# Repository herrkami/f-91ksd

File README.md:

# F-91KSD

F-91KSD is a functional and optical modification of the Casio® F-91W.

**Hardware and firmware are heavily based on the brilliant
[pluto](https://github.com/carrotIndustries/pluto) project.**

## Features
- Multiple chainable countdown timers
- Multiple alarms
- Pulsar app: tap button to measure BPMs and define LED animation
- Consistent and direct user interface
- Three bright LEDs for better readability, blinkiness, and silent alarms
- Stopwatch
- RTTTL ringtones for alarm sounds including some custom sci/fi sounds
- Extensive customisation (key beep frequency and duration, etc.)
- Watch can be calibrated (drift < 1s per month)
- Displays time in decimal/binary/hexadecimal base
- greater than 1 year battery life (estimate based on current consumption)

## Differences to [pluto](https://github.com/carrotIndustries/pluto)
- New PCB (designed in Eagle)
- No compass, no IR receiver, no OTP generation
- Three LEDs including a flash light
- Different menu structure (more Casio-oriented, less menu diving)
- Chainable countdowns
- Optical alarms
- BPM measurement and optical/acoustical metronome
- Some minor bug fixes

## In progress
Battery monitoring isn't functional yet. 

# Credits
Without previous work by [carrotIndustries](https://github.com/carrotIndustries/) and [sh-ow](https://github.com/sh-ow) this project wouldn't exist.
Most of the software components are their work.

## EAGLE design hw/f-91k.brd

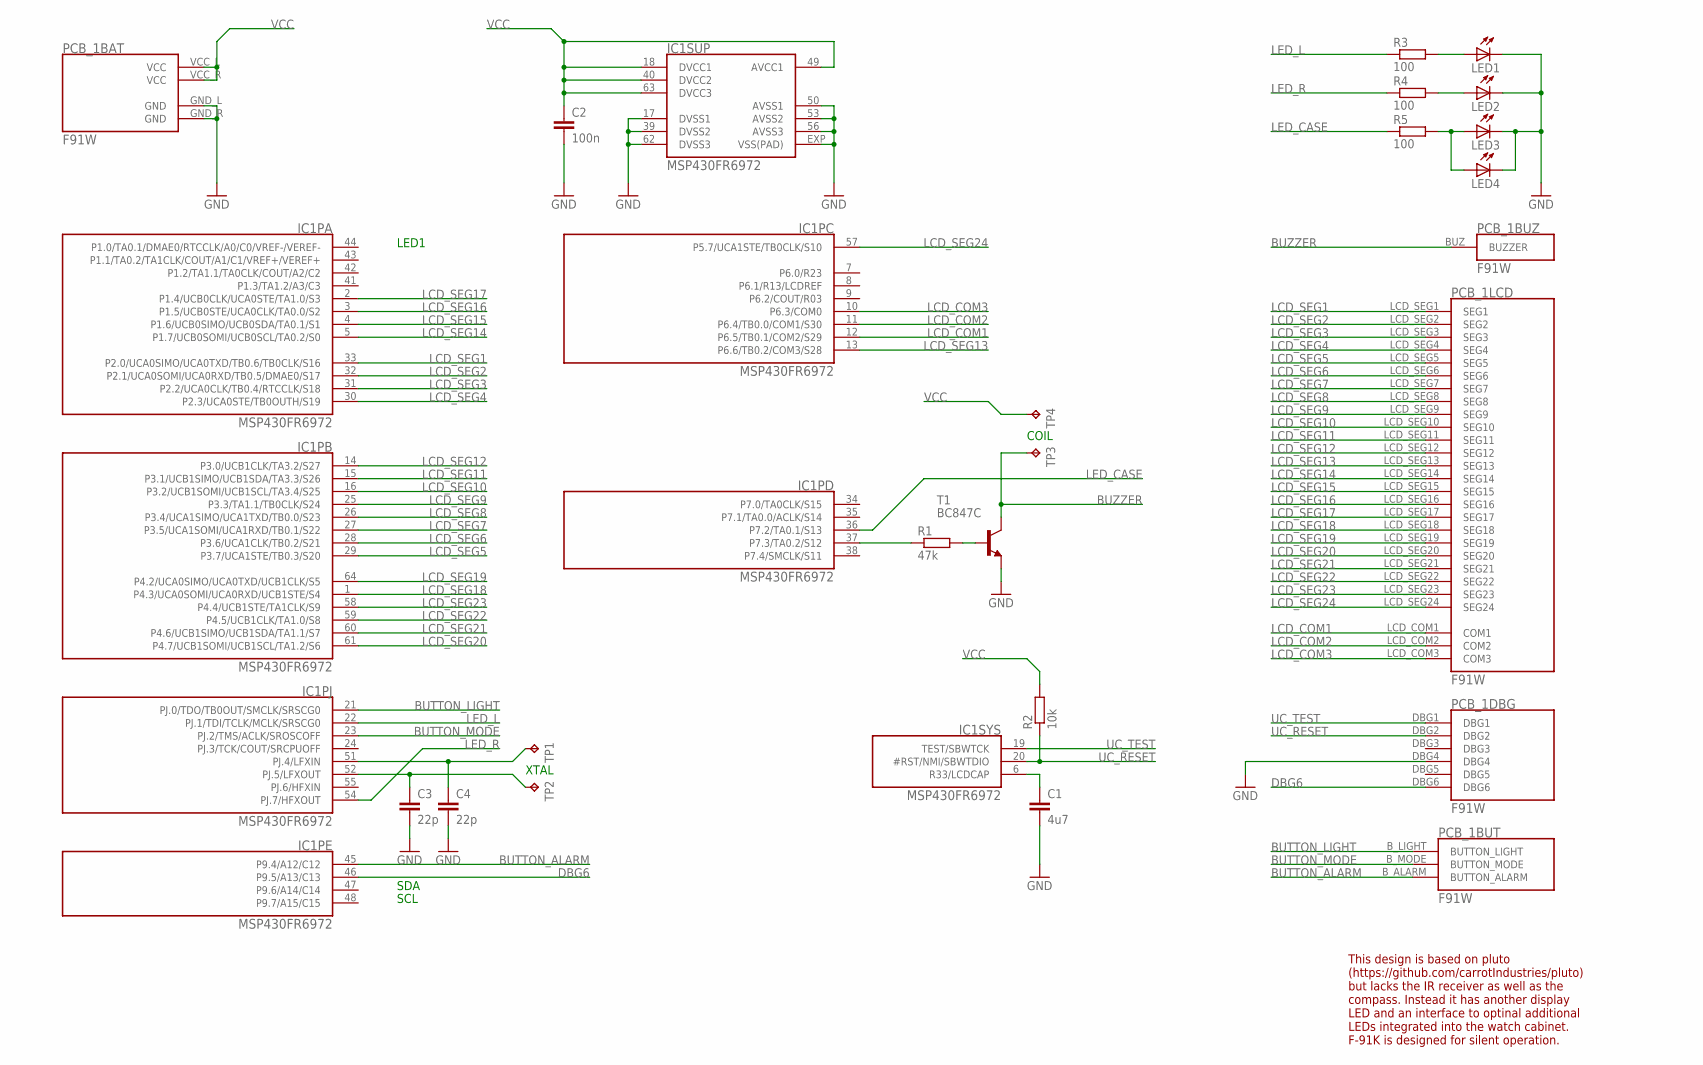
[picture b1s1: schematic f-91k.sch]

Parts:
C1: 4u7; C0603-WW
C2: 100n; C0603-WW
C3, C4: 22p; C0603-WW
IC1: MSP430FR6972; QFN64-9X9
LED1, LED2: LEDCHIPLED_0805; CHIPLED_0805
LED3, LED4: LEDCHIPLED_0603; CHIPLED_0603
PCB_1: F91W
R1: 47k; R0603-WW
R2: 10k; R0603-WW
R3, R4, R5: 100; R0603-WW
T1: BC847C; SOT23-BEC
TP1, TP2: TPTP07SQ; TP07SQ
TP3, TP4: TPTP11SQ; TP11SQ

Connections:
BUTTON_ALARM: IC1.45 (P9.4/A12/C12), PCB_1.B_ALARM (BUTTON_ALARM)
BUTTON_LIGHT: IC1.21 (PJ.0/TDO/TB0OUT/SMCLK/SRSCG0), PCB_1.B_LIGHT (BUTTON_LIGHT)
BUTTON_MODE: IC1.23 (PJ.2/TMS/ACLK/SROSCOFF), PCB_1.B_MODE (BUTTON_MODE)
BUZZER: PCB_1.BUZ (BUZZER), T1.C, TP3.TP
DBG6: IC1.46 (P9.5/A13/C13), PCB_1.DBG6
GND: C1.2, C2.2, C3.2, C4.2, IC1.17 (DVSS1), IC1.39 (DVSS2), IC1.50 (AVSS1), IC1.53 (AVSS2), IC1.56 (AVSS3), IC1.62 (DVSS3), IC1.EXP (VSS(PAD)), LED1.C, LED2.C, LED3.C, LED4.C, PCB_1.DBG4, PCB_1.GND_L (GND), PCB_1.GND_R (GND), T1.E
LCD_COM1: IC1.12 (P6.5/TB0.1/COM2/S29), PCB_1.LCD_COM1 (COM1)
LCD_COM2: IC1.11 (P6.4/TB0.0/COM1/S30), PCB_1.LCD_COM2 (COM2)
LCD_COM3: IC1.10 (P6.3/COM0), PCB_1.LCD_COM3 (COM3)
LCD_SEG1: IC1.33 (P2.0/UCA0SIMO/UCA0TXD/TB0.6/TB0CLK/S16), PCB_1.LCD_SEG1 (SEG1)
LCD_SEG2: IC1.32 (P2.1/UCA0SOMI/UCA0RXD/TB0.5/DMAE0/S17), PCB_1.LCD_SEG2 (SEG2)
LCD_SEG3: IC1.31 (P2.2/UCA0CLK/TB0.4/RTCCLK/S18), PCB_1.LCD_SEG3 (SEG3)
LCD_SEG4: IC1.30 (P2.3/UCA0STE/TB0OUTH/S19), PCB_1.LCD_SEG4 (SEG4)
LCD_SEG5: IC1.29 (P3.7/UCA1STE/TB0.3/S20), PCB_1.LCD_SEG5 (SEG5)
LCD_SEG6: IC1.28 (P3.6/UCA1CLK/TB0.2/S21), PCB_1.LCD_SEG6 (SEG6)
LCD_SEG7: IC1.27 (P3.5/UCA1SOMI/UCA1RXD/TB0.1/S22), PCB_1.LCD_SEG7 (SEG7)
LCD_SEG8: IC1.26 (P3.4/UCA1SIMO/UCA1TXD/TB0.0/S23), PCB_1.LCD_SEG8 (SEG8)
LCD_SEG9: IC1.25 (P3.3/TA1.1/TB0CLK/S24), PCB_1.LCD_SEG9 (SEG9)
LCD_SEG10: IC1.16 (P3.2/UCB1SOMI/UCB1SCL/TA3.4/S25), PCB_1.LCD_SEG10 (SEG10)
LCD_SEG11: IC1.15 (P3.1/UCB1SIMO/UCB1SDA/TA3.3/S26), PCB_1.LCD_SEG11 (SEG11)
LCD_SEG12: IC1.14 (P3.0/UCB1CLK/TA3.2/S27), PCB_1.LCD_SEG12 (SEG12)
LCD_SEG13: IC1.13 (P6.6/TB0.2/COM3/S28), PCB_1.LCD_SEG13 (SEG13)
LCD_SEG14: IC1.5 (P1.7/UCB0SOMI/UCB0SCL/TA0.2/S0), PCB_1.LCD_SEG14 (SEG14)
LCD_SEG15: IC1.4 (P1.6/UCB0SIMO/UCB0SDA/TA0.1/S1), PCB_1.LCD_SEG15 (SEG15)
LCD_SEG16: IC1.3 (P1.5/UCB0STE/UCA0CLK/TA0.0/S2), PCB_1.LCD_SEG16 (SEG16)
LCD_SEG17: IC1.2 (P1.4/UCB0CLK/UCA0STE/TA1.0/S3), PCB_1.LCD_SEG17 (SEG17)
LCD_SEG18: IC1.1 (P4.3/UCA0SOMI/UCA0RXD/UCB1STE/S4), PCB_1.LCD_SEG18 (SEG18)
LCD_SEG19: IC1.64 (P4.2/UCA0SIMO/UCA0TXD/UCB1CLK/S5), PCB_1.LCD_SEG19 (SEG19)
LCD_SEG20: IC1.61 (P4.7/UCB1SOMI/UCB1SCL/TA1.2/S6), PCB_1.LCD_SEG20 (SEG20)
LCD_SEG21: IC1.60 (P4.6/UCB1SIMO/UCB1SDA/TA1.1/S7), PCB_1.LCD_SEG21 (SEG21)
LCD_SEG22: IC1.59 (P4.5/UCB1CLK/TA1.0/S8), PCB_1.LCD_SEG22 (SEG22)
LCD_SEG23: IC1.58 (P4.4/UCB1STE/TA1CLK/S9), PCB_1.LCD_SEG23 (SEG23)
LCD_SEG24: IC1.57 (P5.7/UCA1STE/TB0CLK/S10), PCB_1.LCD_SEG24 (SEG24)
LED_CASE: IC1.36 (P7.2/TA0.1/S13), R5.1
LED_L: IC1.22 (PJ.1/TDI/TCLK/MCLK/SRSCG0), R3.1
LED_R: IC1.54 (PJ.7/HFXOUT), R4.1
unnamed: C1.1, IC1.6 (R33/LCDCAP)
unnamed: IC1.37 (P7.3/TA0.2/S12), R1.1
unnamed: C4.1, IC1.51 (PJ.4/LFXIN), TP1.TP
unnamed: C3.1, IC1.52 (PJ.5/LFXOUT), TP2.TP
unnamed: R1.2, T1.B
unnamed: LED3.A, LED4.A, R5.2
unnamed: LED1.A, R3.2
unnamed: LED2.A, R4.2
UC_RESET: IC1.20 (#RST/NMI/SBWTDIO), PCB_1.DBG2, R2.1
UC_TEST: IC1.19 (TEST/SBWTCK), PCB_1.DBG1
VCC: C2.1, IC1.18 (DVCC1), IC1.40 (DVCC2), IC1.49 (AVCC1), IC1.63 (DVCC3), PCB_1.VCC_L (VCC), PCB_1.VCC_R (VCC), R2.2, TP4.TP

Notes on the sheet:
SDA
SCL
LED1
XTAL
COIL
This design is based on pluto (https://github.com/carrotIndustries/pluto) but lacks the IR receiver as well as the compass. Instead it has another display LED and an interface to optinal additional LEDs integrated into the watch cabinet. F-91K is designed for silent operation.

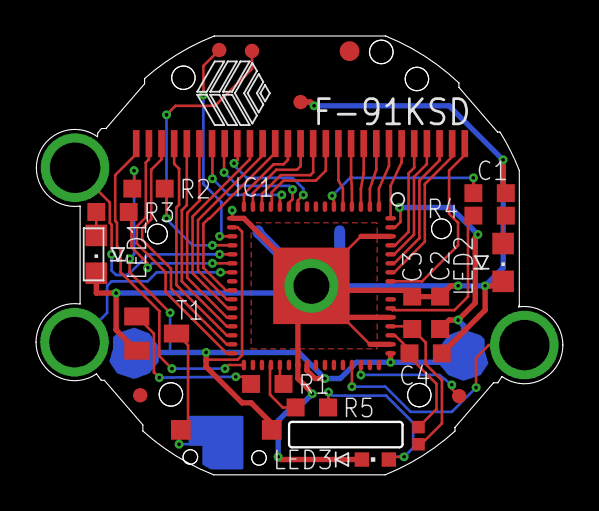
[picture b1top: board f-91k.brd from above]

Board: 2 copper layers, 29.2 x 24.3 mm, 20 parts (1 on the bottom side), 47 nets.

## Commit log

2021-04-15 Initial commit of the koseidai version
2021-04-16 Change directory structure and add hardware design files
2021-04-16 Modify READMEs
2021-04-16 Change time zone menu text from adj to zone
2021-04-16 Add service routine modifications for chaining mode to countdown timers
2021-04-17 Implement menu for timer chaining
2021-04-17 Add keybindings so simulator
2021-04-17 Make menu headers blinking, add silent melody, and remove print commands from emulator
2021-04-18 Add pause to timers
2021-04-21 Add MCU/simulation compiler flag for default LED on duration
2021-04-21 Add pulsar
2021-04-22 Add basic pulsar app
2021-04-22 Add offset option to t adjust menu
2021-04-22 Add BPM capture
2021-04-22 Change BPM capture algorithm
2021-04-22 Add note values
2021-04-22 Add sequence menu to pulsar
2021-04-23 Improve pulsar app
2021-04-23 Extend short LED flashes to become visible in emulator
2021-04-23 Rename hour adjustment app
2021-04-23 Add better time adjusment app
2021-04-24 Workaround missing tap bug in pulsar
2021-04-24 Fix pulsar tap miss
2021-04-25 Further improve pulsar app and add sketch for RTC clock derivation
2021-04-27 Add soft PWM backlight routine
2021-04-27 Change menu strucutre
2021-05-09 Set standard GTK version to 3.0 and fix pulsar sequence adjustments
2021-05-09 Add pulsar sequences as alarm and countdown events
2021-05-09 Make long menu button press always a leaving event and remove OTP
2021-05-09 Add melody and pulsar preview to countdown and alarm selection menus
2021-05-13 Make pulsar grab the sequence speed from pulse pattern and remove sources only required for OTP
2021-05-13 Fix melody bug
2021-05-13 Add popup in time display when counters are running
2021-05-19 Limit brightness levels to 4 stages and change some default parameters
2021-05-19 Improve timer popup notification
2021-05-19 Add flashlight service in backlight routine
2021-05-19 Improve flashlight app behavior
2021-05-19 Slightly improve menus and change number confirm to long enter press
2021-05-23 Modify melodies and efficient melody tester
2021-05-23 Add beeping metronome to pulsar
2021-05-24 Fix flashlight and return consistency
2021-05-24 Improve second adjustment and preserve subseconds when setting RTC
2021-05-26 Modify default user values
2021-05-26 Add special function to alarm app that sets the current time and day of the week as alarm
2021-05-26 Make led routine more efficient
2021-05-26 Correct metronome speed by dividing it by four
2021-05-26 Toggle metronome on long enter press in pulsar app
2021-05-27 Add alarm- and timer-specific metronome enable option
2021-05-27 Improve metronome multiplier
2021-05-30 Improve beep routine
2021-06-08 Fix more-than-eight-timers bug
2021-06-08 Add melody preview to config menu
2021-06-08 Add one alarm such that there are 11 intotal
2021-06-11 Change timer default values
2021-10-24 Update readmes
2021-10-24 Fix typo
2021-10-24 Add credit notice
2021-10-24 Add battery monitoring
2021-10-24 Add note about battery monitoring
